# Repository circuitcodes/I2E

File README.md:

# Introduction to Electronics

Hello!

This is a small practical course in Electronics, following these theoretical lessons:
https://www.youtube.com/playlist?list=PLhNzYIgWJ-jYKyFQY17kkuvdsiJDYk2cP

## What you need
In order to be able to run the experiments you need:
1. Any computer (Windows, Linux or Mac), **better if it is a laptop** (because it can run on batteries):

2. An **Arduino UNO** board (or others compatible boards) + a breadboard + some basic electronic components. I have this kit:

3. The **Arduino IDE** software platform: https://www.arduino.cc/en/software

4. The **Processing** software platform (use last **STABLE** version): https://processing.org/

5. The **Kicad** EDA software suite: https://www.kicad.org/

For the **Bioamplifier** experiment you also need:
1. some (at least 3) skin patch electrodes (e.g. https://www.biopac.com/product/general-purpose-electrodes/)

2. Three alligator clamps, for the connection to the electrodes:

3. one glorious :) TL084 operational amplifier:

I have also modified the trimmers I use in these experiments, by soldering them on a small PCB like this one:

...it's not strictly necessary but it helps a lot, otherwise it might be difficult to insert it on the breadboard!

## What to do now
The easiest thing to do now, is go here:

and download the ZIP file on your PC.

In order to run the **Bioamplifier** experiment, you need to install the **ControlP5** library of **Processing**. So, you launch Processing and then you do the following things:
1. Realize that the library is missing:

2. Go to **add library**:

3. Install the library:

4. Verify the library has been installed:

5. In the **Serialplotter.pde** code, set the correct serial port for Arduino:

After all this, you should be able to run the **Serialplotter** app you need to visualize the analog signals from Arduino:

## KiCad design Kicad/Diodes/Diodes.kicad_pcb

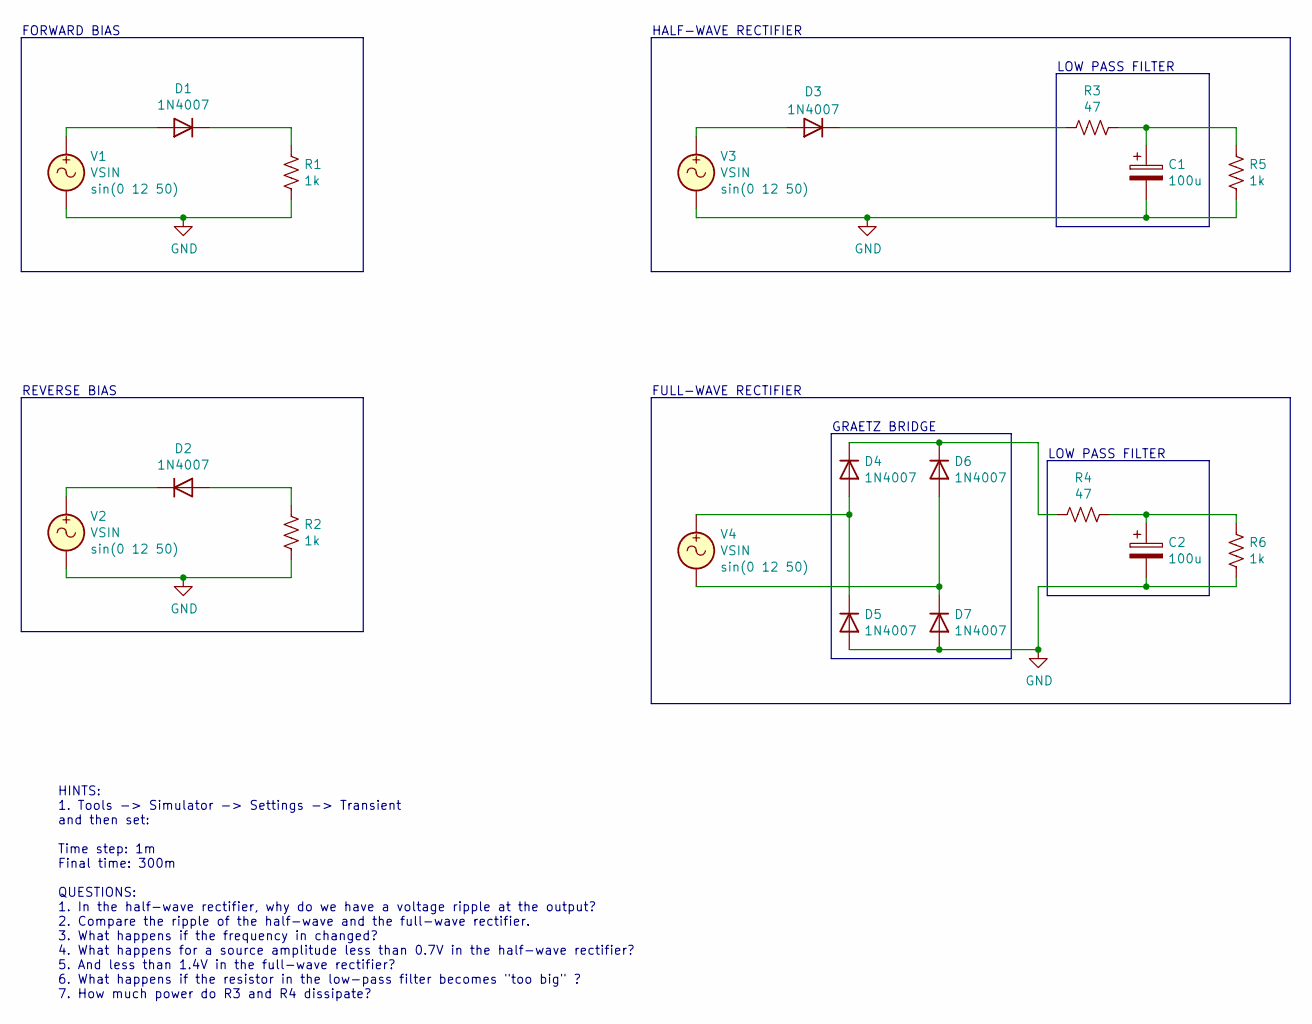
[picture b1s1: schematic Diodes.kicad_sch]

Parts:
C1, C2: 100u; CP_Radial_D8.0mm_P3.50mm
D1, D2, D3, D4, D5, D6, D7: 1N4007; D_DO-15_P12.70mm_Horizontal
R1, R2, R5, R6: 1k; R_Axial_DIN0204_L3.6mm_D1.6mm_P7.62mm_Horizontal
R3, R4: 47; R_Axial_DIN0204_L3.6mm_D1.6mm_P7.62mm_Horizontal
V1, V2, V3, V4: VSIN; TerminalBlock_bornier-2_P5.08mm

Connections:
GND: C1.2, C2.2, D5.2 (A), D7.2 (A), R1.2, R2.2, R5.2, R6.2, V1.2, V2.2, V3.2
unnamed: C1.1, R3.2, R5.1
unnamed: C2.1, R4.2, R6.1
unnamed: D1.1 (K), R1.1
unnamed: D1.2 (A), V1.1
unnamed: D2.1 (K), V2.1
unnamed: D2.2 (A), R2.1
unnamed: D3.1 (K), R3.1
unnamed: D3.2 (A), V3.1
unnamed: D4.1 (K), D6.1 (K), R4.1
unnamed: D4.2 (A), D5.1 (K), V4.1
unnamed: D6.2 (A), D7.1 (K), V4.2

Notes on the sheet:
LOW PASS FILTER
HINTS: 1. Tools -> Simulator -> Settings -> Transient and then set: Time step: 1m Final time: 300m QUESTIONS: 1. In the half-wave rectifier, why do we have a voltage ripple at the output? 2. Compare the ripple of the half-wave and the full-wave rectifier. 3. What happens if the frequency in changed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
FULL-WAVE RECTIFIER
GRAETZ BRIDGE
REVERSE BIAS
HALF-WAVE RECTIFIER
FORWARD BIAS

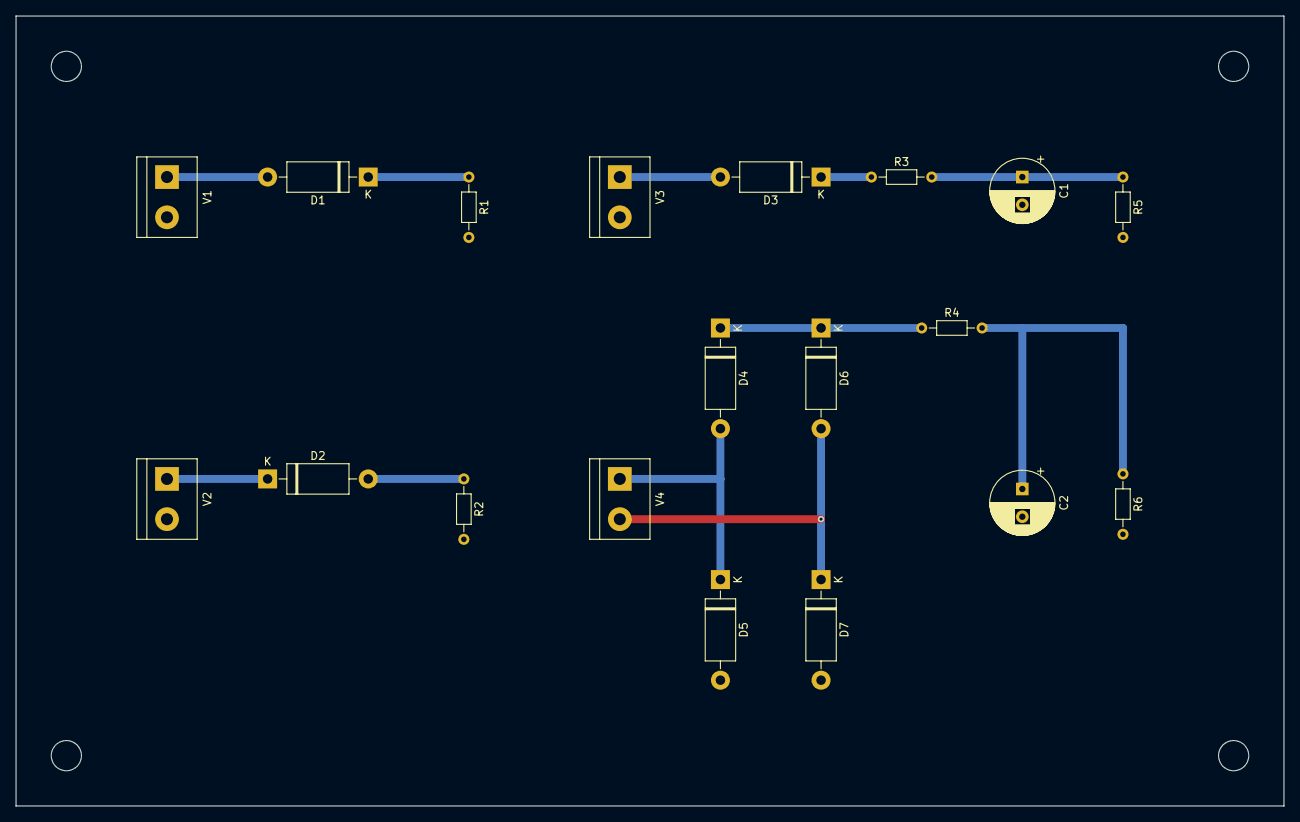
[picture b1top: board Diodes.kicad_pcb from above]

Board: 2 copper layers, 160.0 x 99.7 mm, 19 parts (0 on the bottom side), 12 nets.

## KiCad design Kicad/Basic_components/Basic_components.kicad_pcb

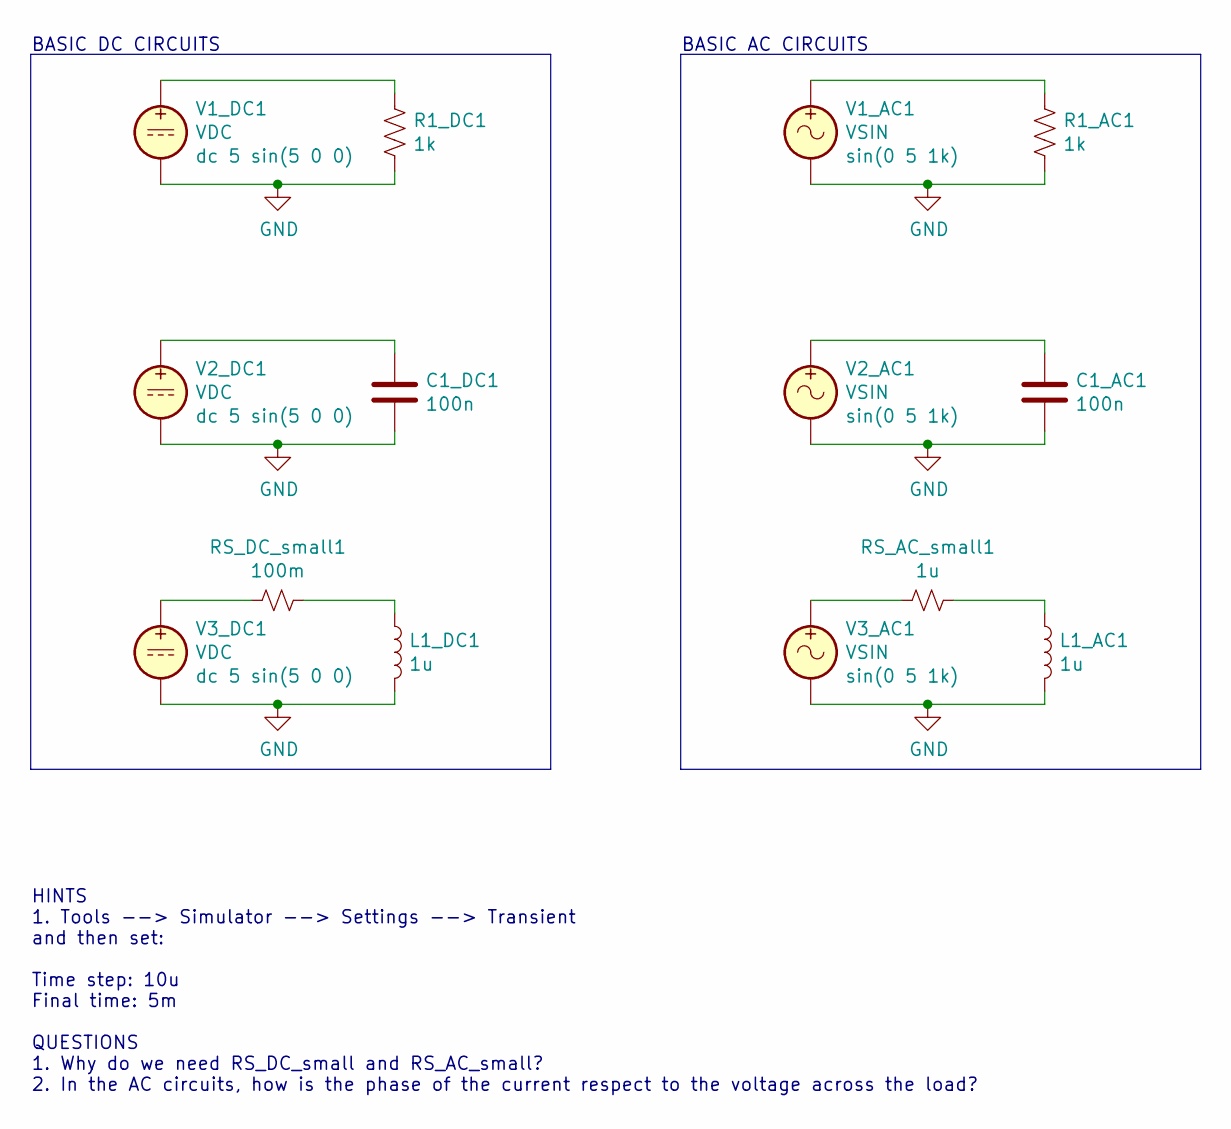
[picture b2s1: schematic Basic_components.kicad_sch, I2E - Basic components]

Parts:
C1_AC1, C1_DC1: 100n; C_Rect_L7.0mm_W2.0mm_P5.00mm
L1_AC1, L1_DC1: 1u; L_Axial_L5.3mm_D2.2mm_P7.62mm_Horizontal_Vishay_IM-1
R1_AC1, R1_DC1: 1k; R_Axial_DIN0204_L3.6mm_D1.6mm_P7.62mm_Horizontal
RS_AC_small1: 1u; R_Axial_DIN0204_L3.6mm_D1.6mm_P7.62mm_Horizontal
RS_DC_small1: 100m; R_Axial_DIN0204_L3.6mm_D1.6mm_P7.62mm_Horizontal
V1_AC1, V2_AC1, V3_AC1: VSIN; TerminalBlock_bornier-2_P5.08mm
V1_DC1, V2_DC1, V3_DC1: VDC; TerminalBlock_bornier-2_P5.08mm

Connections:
GND: C1_AC1.2, C1_DC1.2, L1_AC1.2, L1_DC1.2, R1_AC1.1, R1_DC1.1, V1_AC1.2, V1_DC1.2, V2_AC1.2, V2_DC1.2, V3_AC1.2, V3_DC1.2
unnamed: C1_AC1.1, V2_AC1.1
unnamed: C1_DC1.1, V2_DC1.1
unnamed: L1_AC1.1, RS_AC_small1.1
unnamed: L1_DC1.1, RS_DC_small1.1
unnamed: R1_AC1.2, V1_AC1.1
unnamed: R1_DC1.2, V1_DC1.1
unnamed: RS_AC_small1.2, V3_AC1.1
unnamed: RS_DC_small1.2, V3_DC1.1

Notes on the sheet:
HINTS 1. Tools --> Simulator --> Settings --> Transient and then set: Time step: 10u Final time: 5m QUESTIONS 1. Why do we need RS_DC_small and RS_AC_small? 2. In the AC circuits, how is the phase of the current respect to the voltage across the load?
BASIC DC CIRCUITS
BASIC AC CIRCUITS

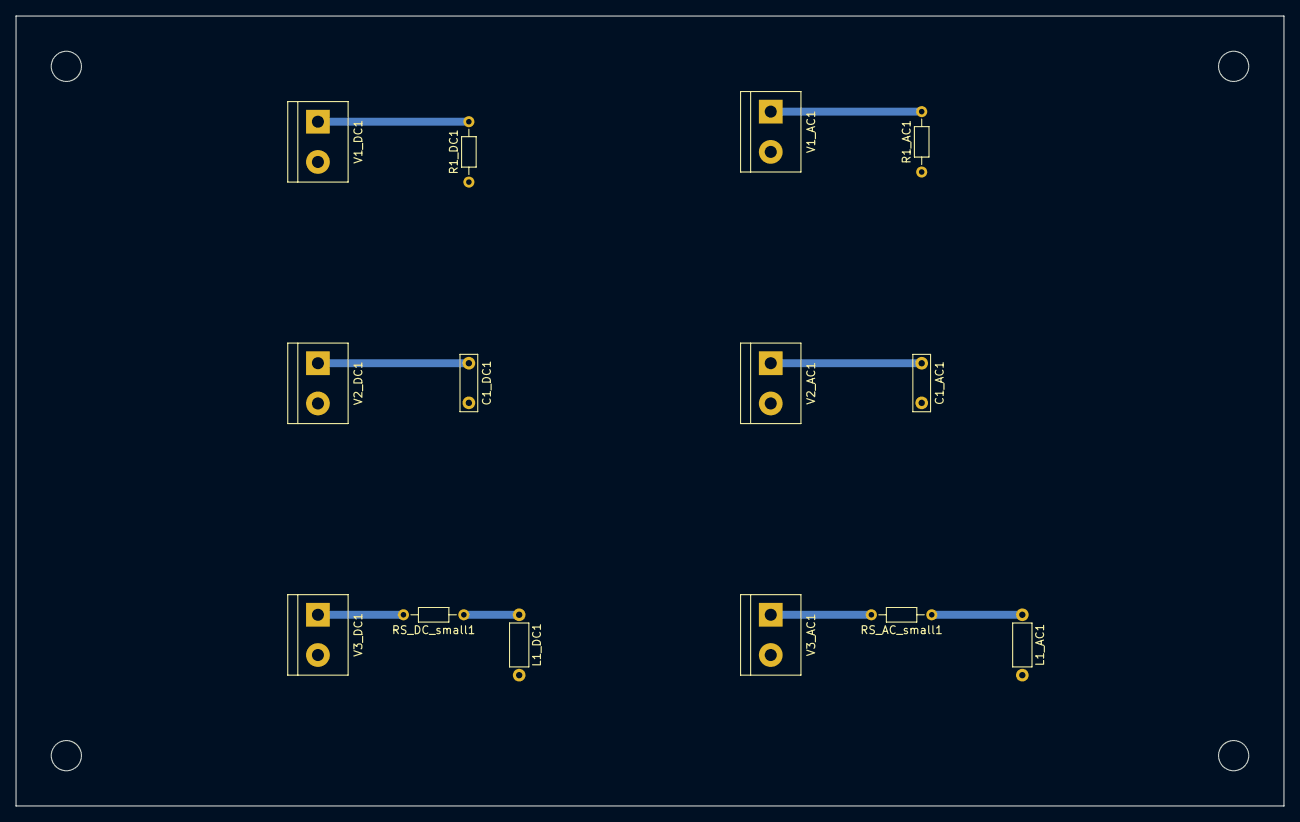
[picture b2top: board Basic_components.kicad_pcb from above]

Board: 2 copper layers, 160.0 x 99.7 mm, 14 parts (0 on the bottom side), 9 nets.

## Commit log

2022-01-27 Added all files from USB drive.
2022-01-27 Added images and Serialplotter for Biopotential.
2022-01-27 Added documentation.
2022-01-27 Working on Readme.
2022-01-27 Adding docs.
2022-01-27 File renamed.
2022-01-28 Implemented log file in Serialplotter.
2022-02-21 Fixed cp5 bug in biopotential processing code.
2022-02-21 Update Kicad projects to Kicad v6.0.
